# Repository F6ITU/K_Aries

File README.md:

# K_Aries

Aries, an OpenHPSDR ATU (kicad version) 

The golden fleece ram (Aries in Latin, Chrysomallos -Χρυσόμαλλος- in ancien Greek) 
has been send by Hermes (codename of the first "mono board" OpenHPSDR) to save Phrixos and Hellé. 
After his death, his remains (the golden fleece) was conquered by Jason and the Argonauts

 This repository is a fork of the Aries ATU project designed by Kjell Karlsen LA2NI and Laurence Barker G8NJJ.
 
 The original work can be downloaded from

https://github.com/LA2NI/

https://github.com/laurencebarker

A French version of the main documentation and user's note could be found in the "Documentation" directory 
(still work in progress)

Main differences are : 

* - DIL footprint  for the I2C ram (hard to find in SOIC package)
* - R19 trace bug corrected
* - input-output coax connector changed (Amphenol bnc straight with reference)
* - F-CU ground "forbiden zone" modified around tandem match output (R42-E42-R1-R2 of the original design)
* - dual footprint for 12V input J4 (Molex kk 2.54mm and Phoenix high current "board to wire" connector)
* - same Tianbo TRA2 L-12VDC-S-Z relay (or Omron G2R-1-E DC12) used for antenna switch 
( Total relay count is 21 Tinabo TRA2/Omron G2R and 1 G6A-274P-ST-US DC12 now)

# Work is RTM
These files are considered as "ready to manufacture". In other words, Gerber files, iBom and BOM could be downloaded and/or
sent to a fabhouse 

No prototype of this version have been assembled and tested so far. Use it at your own risk, even if I did my best to kill every
bug detected by the DRC

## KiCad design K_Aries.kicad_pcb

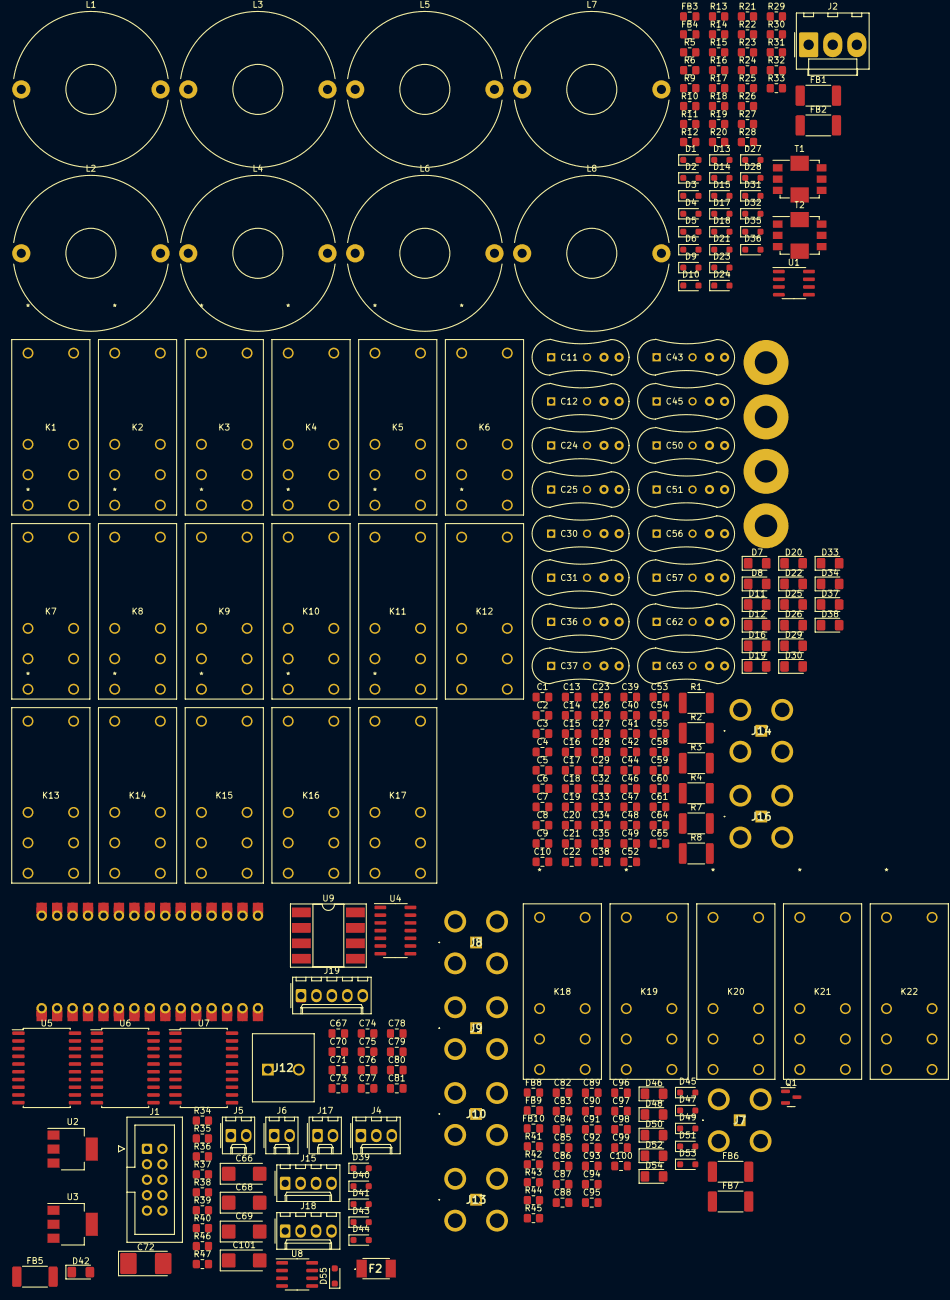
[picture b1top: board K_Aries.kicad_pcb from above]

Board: 2 copper layers, 278 parts (0 on the bottom side), 145 nets, no tracks yet.

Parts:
C1, C3, C4, C7, C8, C9, C10, C14, C15, C16, C18, C19, C20, C21, C22, C23, C26, C27, C28, C29, C32, C33, C34, C35, C38, C39, C40, C41, C42, C44, C46, C47, C48, C49, C52, C53, C54, C55, C58, C59, C60, C61, C64, C65, C67, C70, C73, C75, C76, C77, C78, C80, C82, C84, C85, C87, C88, C89, C90, C91, C92, C93, C94, C95, C96, C97, C98, C99, C100: 10n; C_0805_2012Metric_Pad1.18x1.45mm_HandSolder
C2, C17, C79, C81, C83, C86: 100n; C_0805_2012Metric_Pad1.18x1.45mm_HandSolder
C5: 1u; C_0805_2012Metric_Pad1.18x1.45mm_HandSolder
C6, C13, C71, C74: 10u; C_0805_2012Metric_Pad1.18x1.45mm_HandSolder
C11, C12: 18p; Capacitor_Mica
C24, C25: 39p; Capacitor_Mica
C30, C31: 82p; Capacitor_Mica
C36, C37: 160p; Capacitor_Mica
C43, C45: 330p; Capacitor_Mica
C50, C51: 660p; Capacitor_Mica
C56, C57: 1320p; Capacitor_Mica
C62, C63: 2640p; Capacitor_Mica
C66, C68, C69, C101: 10u/35V; CP_EIA-6032-28_Kemet-C_Pad2.25x2.35mm_HandSolder
C72: 100u/10V; CP_EIA-7132-28_AVX-C_Pad2.72x3.50mm_HandSolder
D1, D2, D3, D4: 1N5711; D_SOD-323_HandSoldering
D5, D6, D9, D10, D13, D14, D15, D17, D18, D21, D23, D24, D27, D28, D31, D32, D35, D36, D39, D40, D41, D43, D44, D45, D47, D49, D51, D53: BAS16J; D_SOD-323_HandSoldering
D7, D8, D11, D12, D16, D19, D20, D22, D25, D26, D29, D30, D33, D34, D37, D38, D42, D46, D48, D50, D52, D54: LED_Small; LED_1206_3216Metric_Pad1.42x1.75mm_HandSolder
D55: 1SS355VM; D_SOD-323_HandSoldering
F2: MF-MSMF110_24X-2; MFMSMF11024X2
FB1, FB2, FB5, FB6, FB7: FerriteBead_Small; L_2512_6332Metric_Pad1.52x3.35mm_HandSolder
FB3, FB4, FB8, FB9, FB10: FerriteBead_Small; L_0805_2012Metric_Pad1.15x1.40mm_HandSolder
H1, H2, H3, H4: MountingHole_Pad; MountingHole_3.7mm_Pad
J1: To Protec_Brd; IDC-Header_2x05_P2.54mm_Vertical
J2: Conn_01x03; Molex_KK-396_A-41791-0003_1x03_P3.96mm_Vertical
J4: Power_In; Molex_KK-254_AE-6410-03A_1x03_P2.54mm_Vertical
J5, J6, J17: Conn_01x02; Molex_KK-254_AE-6410-02A_1x02_P2.54mm_Vertical
J7, J8, J9, J10, J13, J14, J16: Conn_Coaxial; BNC_Amphenol_031532951RFX
J12: Conn_01x02; 1711725
J15: To Display; Molex_KK-254_AE-6410-04A_1x04_P2.54mm_Vertical
J18: To Protec_Brd encoder; Molex_KK-254_AE-6410-04A_1x04_P2.54mm_Vertical
J19: To P.A.; Molex_KK-254_AE-6410-05A_1x05_P2.54mm_Vertical
K1, K2, K3, K4, K5, K6, K7, K8, K9, K10, K11, K12, K13, K14, K15, K16, K17, K18, K19, K20, K21, K22: G2R-1-E DC12; RELAY_G2R-1-E AC12
L1, L2, L3, L4, L5, L6, L7, L8: L_Iron_Small; L_Toroid_Horizontal_D25.4mm_P22.90mm_Vishay_TJ5_BigPads
Q1: 2N7002; SOT-23
R1, R2, R3, R4, R7, R8: 100R; R_1812_4532Metric_Pad1.30x3.40mm_HandSolder
R5, R6: 100k; R_0805_2012Metric_Pad1.20x1.40mm_HandSolder
R9, R10: 1k; R_0805_2012Metric_Pad1.20x1.40mm_HandSolder
R11, R12: 22k; R_0805_2012Metric_Pad1.20x1.40mm_HandSolder
R13, R14, R19, R20, R21, R22, R23, R24, R25, R26, R27, R28, R29, R30, R31, R32, R33, R41, R42, R43, R44, R45: 2k7; R_0805_2012Metric_Pad1.20x1.40mm_HandSolder
R15, R16: 15k; R_0805_2012Metric_Pad1.20x1.40mm_HandSolder
R17, R18: 18k; R_0805_2012Metric_Pad1.20x1.40mm_HandSolder
R34, R35, R36, R38, R39, R40, R46, R47: 10k; R_0805_2012Metric_Pad1.20x1.40mm_HandSolder
R37: 1K; R_0805_2012Metric_Pad1.20x1.40mm_HandSolder
T1, T2: CST1; Transformer_Coilcraft_CST1
U1: LM358; SOIC-8_3.9x4.9mm_P1.27mm
U2: LM1117S-5.0; SOT-223-3_TabPin2
U3: LM1117S-3.3; SOT-223-3_TabPin2
U4: 74HCT04; SOIC-14_3.9x8.7mm_P1.27mm
U5, U6, U7: TPIC6595; SOIC-20W_7.5x12.8mm_P1.27mm
U8: 24FC1025-I_SN; SOIC-8_3.9x4.9mm_P1.27mm
U9: 24FC1025-I_SN; DIP-8_W8.89mm_SMDSocket_LongPads
U12: Arduino-NANO-33; NANO_33_Socket_Castell

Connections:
+3.3V: C74.1, C77.1, R34.1, R35.1, R36.1, R38.1, R39.1, R40.1, R46.2, R47.2, U3.2 (VO), U8.8 (VCC), U9.8 (VCC), U12.17
+5V: C72.1, C78.1, C79.1, C80.1, C81.1, J15.1, U2.2 (VO), U4.14 (VCC), U5.2 (VCC), U5.8 (~SRCLR), U6.2 (VCC), U6.8 (~SRCLR), U7.2 (VCC), U7.8 (~SRCLR)
+12V: C1.1, C2.1, C13.2, C14.2, C17.2, C68.1, C69.1, C71.1, FB1.1, FB2.1, FB5.2, U1.8 (V+), U2.3 (VI), U3.3 (VI)
+12V_R: C5.1, C15.1, C26.1, C32.1, C39.1, C44.1, C46.1, C52.1, C58.1, C64.1, C82.1, C83.1, D5.1 (K), D7.2 (A), D9.1 (K), D11.2 (A), D13.1 (K), D15.2 (A), D17.1 (K), D19.2 (A), D21.1 (K), D22.2 (A), D23.1 (K), D25.2 (A), D27.1 (K), D29.2 (A), D31.1 (K), D33.2 (A), D35.1 (K), D37.2 (A), FB1.2, FB6.1, K1.1, K3.1, K5.1, K7.1, K9.1, K10.1, K12.1, K14.1, K16.1
A6: J19.1, U12.25
A7: J19.2, U12.26
ANT1: C92.1, FB8.1, U7.4 (DRAIN0)
ANT2: C96.1, FB9.1, U7.5 (DRAIN1)
ANT3: C99.1, FB10.1, U7.6 (DRAIN2)
ATU_IN: C12.2, C25.2, C31.2, C37.2, C45.2, C51.2, C57.2, C63.2, J2.2, K9.2, K9.7, T1.7
ATU_OUT: J16.1 (In), K9.4, K9.5, K16.2, K16.7, K19.4, K19.5, L8.2
CAPOUT: C38.1, D21.2 (A), K9.8, R25.1, U7.7 (DRAIN3)
Cap1: C10.1, D6.2 (A), K2.8, R14.1
Cap2: C23.1, D10.2 (A), K4.8, R20.1
Cap3: C29.1, D14.2 (A), K6.8, R22.1
Cap4: C35.1, D18.2 (A), K8.8, R24.1
Cap5: C42.1, D24.2 (A), K11.8, R27.1
Cap6: C49.1, D28.2 (A), K13.8, R29.1
Cap7: C55.1, D32.2 (A), K15.8, R31.1
Cap8: C61.1, D36.2 (A), K17.8, R33.1
D2_A: D43.1 (K), J1.3
D5_B: D41.1 (K), J1.4
D8: J1.5, U12.11
DATA: R40.2, U4.1, U12.14
ENC1A: J18.1, U12.21
ENC1B: J18.2, U12.22
ENC_PB: J18.3, U12.7
FWD: C20.1, C75.1, FB3.2, J1.8, U12.20
GND: C1.2, C2.2, C3.2, C4.2, C5.2, C6.2, C7.2, C8.2, C9.2, C10.2, C13.1, C14.1, C15.2, C16.2, C17.1, C18.2, C19.2, C20.2, C21.2, C22.2, C23.2, C26.2, C27.2, C28.2, C29.2, C32.2, C33.2, C34.2, C35.2, C38.2, C39.2, C40.2, C41.2, C42.2, C44.2, C46.2, C47.2, C48.2, C49.2, C52.2, C53.2, C54.2, C55.2, C58.2, C59.2, C60.2, C61.2, C64.2, C65.2, C66.2, C67.1, C68.2, C69.2, C70.1, C71.2, C72.2, C73.1, C74.2, C75.2, C76.2, C77.2, C78.2, C79.2, C80.2, C81.2, C82.2, C83.2, C84.2, C85.2, C86.2, C87.2, C88.2, C89.2, C90.2, C91.2, C92.2, C93.2, C94.2, C95.2, C96.2, C97.2, C98.2, C99.2, C100.2, C101.2, D42.1 (K), H1.1, H2.1, H3.1, H4.1, J1.2, J4.2, J5.2, J6.2, J7.2 (Ext), J8.2 (Ext), J9.2 (Ext), J10.2 (Ext), J12.2, J13.2 (Ext), J14.2 (Ext), J15.4, J16.2 (Ext), J17.2, J18.4, J19.5, K2.3, K2.6, K4.3, K4.6, K6.3, K6.6, K8.3, K8.6, K11.3, K11.6, K13.3, K13.6, K15.3, K15.6, K17.3, K17.6, Q1.2 (S), R1.2, R2.1, R3.2, R4.1, R5.2, R6.2, R7.2, R8.2, R11.1, R12.1, R17.2, R18.2, T1.4, T2.6, U1.4 (V-), U2.1 (GND), U3.1 (GND), U4.7 (GND), U5.1 (PGND), U5.9 (~G), U5.10 (PGND), U5.11 (PGND), U5.19 (LGND), U5.20 (PGND), U6.1 (PGND), U6.9 (~G), U6.10 (PGND), U6.11 (PGND), U6.19 (LGND), U6.20 (PGND), U7.1 (PGND), U7.9 (~G), U7.10 (PGND), U7.11 (PGND), U7.19 (LGND), U7.20 (PGND), U8.2 (A1), U8.3 (A2), U8.4 (VSS), U8.7 (WP), U9.2 (A1), U9.3 (A2), U9.4 (VSS), U9.7 (WP), U12.4, U12.29
Ind1: C9.1, D5.2 (A), K1.8, R13.1
Ind2: C22.1, D9.2 (A), K3.8, R19.1
Ind3: C28.1, D13.2 (A), K5.8, R21.1
Ind4: C34.1, D17.2 (A), K7.8, R23.1
Ind5: C41.1, D23.2 (A), K10.8, R26.1
Ind6: C48.1, D27.2 (A), K12.8, R28.1
Ind7: C54.1, D31.2 (A), K14.8, R30.1
Ind8: C60.1, D35.2 (A), K16.8, R32.1
LOAD: R38.2, U4.13, U12.9
unnamed: C11.1, K2.4, K2.5
unnamed: C11.2, C12.1
unnamed: C18.1, FB3.1, R15.2, R17.1
unnamed: C19.1, FB4.1, R16.2, R18.1
unnamed: C24.1, K4.4, K4.5
unnamed: C24.2, C25.1
unnamed: C30.1, K6.4, K6.5
unnamed: C30.2, C31.1
unnamed: C36.1, K8.4, K8.5
unnamed: C36.2, C37.1
unnamed: C43.1, K11.4, K11.5
unnamed: C43.2, C45.1
unnamed: C50.1, K13.4, K13.5
unnamed: C50.2, C51.1
unnamed: C56.1, K15.4, K15.5
unnamed: C56.2, C57.1
unnamed: C62.1, K17.4, K17.5
unnamed: C62.2, C63.1
unnamed: C66.1, F2.2, FB5.1
unnamed: D1.2 (A), R1.1, R3.1, T2.8
unnamed: C3.1, C7.1, D1.1 (K), R5.1, R9.1
unnamed: D2.2 (A), R2.2, R4.2, T1.6, T2.7
unnamed: C4.1, C8.1, D2.1 (K), R6.1, R10.1
unnamed: D3.2 (A), R15.1, U1.7
unnamed: D3.1 (K), R11.2, U1.6 (-)
unnamed: D4.2 (A), R16.1, U1.1
unnamed: D4.1 (K), R12.2, U1.2 (-)
unnamed: D7.1 (K), R13.2
unnamed: D8.1 (K), R14.2
unnamed: C6.1, C16.1, C27.1, C33.1, C40.1, C47.1, C53.1, C59.1, C65.1, D6.1 (K), D8.2 (A), D10.1 (K), D12.2 (A), D14.1 (K), D16.2 (A), D18.1 (K), D20.2 (A), D24.1 (K), D26.2 (A), D28.1 (K), D30.2 (A), D32.1 (K), D34.2 (A), D36.1 (K), D38.2 (A), FB2.2, K2.1, K4.1, K6.1, K8.1, K11.1, K13.1, K15.1, K17.1
unnamed: D11.1 (K), R19.2
unnamed: D12.1 (K), R20.2
unnamed: D15.1 (K), R21.2
unnamed: D16.1 (K), R22.2
unnamed: D19.1 (K), R23.2
unnamed: D20.1 (K), R24.2
unnamed: D22.1 (K), R25.2
unnamed: D25.1 (K), R26.2
unnamed: D26.1 (K), R27.2
unnamed: D29.1 (K), R28.2
unnamed: D30.1 (K), R29.2
unnamed: D33.1 (K), R30.2
unnamed: D34.1 (K), R31.2
unnamed: D37.1 (K), R32.2
unnamed: D38.1 (K), R33.2
unnamed: D39.2 (A), R34.2, U12.15
unnamed: C67.2, D39.1 (K), J17.1
unnamed: C70.2, D40.1 (K), J6.1
unnamed: D42.2 (A), R37.1
unnamed: D43.2 (A), U12.5
unnamed: C88.1, C90.1, D45.2 (A), D47.2 (A), K18.8, K19.8, Q1.3 (D), R41.1, R42.1
unnamed: C84.1, C86.1, C89.1, C91.1, C94.1, C97.1, C100.1, D45.1 (K), D46.2 (A), D47.1 (K), D48.2 (A), D49.1 (K), D50.2 (A), D51.1 (K), D52.2 (A), D53.1 (K), D54.2 (A), FB6.2, K18.1, K19.1, K20.1, K21.1, K22.1
unnamed: D46.1 (K), R41.2
unnamed: D48.1 (K), R42.2
unnamed: C93.1, D49.2 (A), FB8.2, K20.8, R43.1
unnamed: D50.1 (K), R43.2
unnamed: C95.1, D51.2 (A), FB9.2, K21.8, R44.1
unnamed: D52.1 (K), R44.2
unnamed: C98.1, D53.2 (A), FB10.2, K22.8, R45.1
unnamed: D54.1 (K), R45.2
unnamed: C101.1, D55.2 (A), J4.1, J4.3, J12.1
unnamed: D55.1 (K), F2.1
unnamed: J2.1, K1.3, K1.6, L1.1
unnamed: J2.3, R7.1, R8.1
unnamed: J7.1 (In), K20.4, K20.5
unnamed: J8.1 (In), K21.4, K21.5
unnamed: J9.1 (In), K22.4, K22.5
unnamed: J10.1 (In), K18.3, K18.6
unnamed: J13.1 (In), K18.4, K18.5
unnamed: J14.1 (In), T1.8, T2.4
unnamed: K1.2, K1.7, K3.3, K3.6, L1.2, L2.1
unnamed: K3.2, K3.7, K5.3, K5.6, L2.2, L3.1
unnamed: K5.2, K5.7, K7.3, K7.6, L3.2, L4.1
unnamed: K9.3, K9.6
unnamed: K10.2, K10.7, K12.3, K12.6, L5.2, L6.1
unnamed: K7.2, K7.7, K10.3, K10.6, L4.2, L5.1
unnamed: K12.2, K12.7, K14.3, K14.6, L6.2, L7.1
unnamed: K14.2, K14.7, K16.3, K16.6, L7.2, L8.1
unnamed: K18.2, K18.7, K19.2, K19.7
unnamed: K19.3, K19.6, K20.3, K20.6, K21.3, K21.6, K22.3, K22.6
unnamed: K20.2, K20.7
unnamed: K21.2, K21.7
unnamed: K22.2, K22.7
unnamed: C87.1, FB7.2, Q1.1 (G)
unnamed: R37.2, U12.10
unnamed: R39.2, U4.5, U12.16
unnamed: R10.2, U1.3 (+)
unnamed: R9.2, U1.5 (+)
unnamed: U4.2, U4.3
unnamed: U4.6, U4.9
unnamed: U4.11, U4.12
unnamed: U4.4, U5.3 (SER_IN)
unnamed: U5.18 (SER_OUT), U6.3 (SER_IN)
unnamed: U6.18 (SER_OUT), U7.3 (SER_IN)
PTT: D44.2 (A), R36.2, U12.13
PTT_IN: C73.2, D44.1 (K), J1.10, J5.1, J19.4
RCLK: U4.10, U5.12 (RCLK), U6.12 (RCLK), U7.12 (RCLK)
RESET: J1.1, U12.3
REV: C21.1, C76.1, FB4.2, J1.9, U12.19
RX: J15.2, U12.2
SCL: J1.6, R47.1, U8.6 (SCL), U9.6 (SCL), U12.24
SDA: J1.7, R46.1, U8.5 (SDA), U9.5 (SDA), U12.23
SRCK: U4.8, U5.13 (SRCK), U6.13 (SRCK), U7.13 (SRCK)
TUNE: D40.2 (A), R35.2, U12.12
TUNE_PB: D41.2 (A), U12.8
TX: J15.3, U12.1
T/R_PTT: C85.1, FB7.1, U12.6

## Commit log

2023-04-21 first commit, transformer schematic
2023-04-22 vswr and antenna switch schematic added
2023-04-23 schematic fully captured
2023-04-23 component-footprint association
2023-04-24 dual footprint for serial eprom
2023-04-24 all component sourced, all 3D object configured
2023-04-25 TRX relay back to G6A, minor changes
2023-04-26 placement F_Cu complete, starting B_Cu
2023-04-28 more passive component layout, new silkscreen
2023-04-29 all components are placed
2023-05-03 intermediate git, more traces to come
2023-05-10 routing completed, silk to be cleaned
2023-05-10 minor changes in the README file
2023-05-11 many errors fixed after running DRC, pcb clean, silk clean
2023-05-11 RTM release, gerber OK, updated Readme
2023-05-11 iBOM added
2023-05-12 new ibom, schematic pdf, arduino slighly shifted on board's edge
2023-05-12 minor mods, new gerber
2023-05-12 minor schematic mods
2023-07-22 more doc, silver mica bom
